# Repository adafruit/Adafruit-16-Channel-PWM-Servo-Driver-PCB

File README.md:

## Adafruit 16-Channel PWM Servo Driver PCB Eagle Files

<a href="http://www.adafruit.com/products/815"><br/>
Click here to purchase one from the Adafruit shop</a>

This is the PCB for the Adafruit 16-channel PWM/Servo breakout board. Format is EagleCAD schematic and board layout
For more details, check out the product page at
* http://www.adafruit.com/products/815

### Description

You want to make a cool robot, maybe a hexapod walker, or maybe just a piece of art with a lot of moving parts. Or maybe you want to drive a lot of LEDs with precise PWM output. Then you realize that your microcontroller has a limited number of PWM outputs! What now? You could give up OR you could just get this handy PWM and Servo driver breakout.

When we saw this chip, we quickly realized what an excellent add-on this would be. Using only two pins, control 16 free-running PWM outputs! You can even chain up 62 breakouts to control up to 992 PWM outputs (which we would really like to see since it would be glorious)

* It's an i2c-controlled PWM driver with a built in clock. That means that, unlike the TLC5940 family, you do not need to continuously send it signal tying up your microcontroller, its completely free running!
* It is 5V compliant, which means you can control it from a 3.3V microcontroller and still safely drive up to 6V outputs (this is good for when you want to control white or blue LEDs with 3.4+ forward voltages)
* 6 address select pins so you can wire up to 62 of these on a single i2c bus, a total of 992 outputs - that's a lot of servos or LEDs
Adjustable frequency PWM up to about 1.6 KHz
* 12-bit resolution for each output - for servos, that means about 4us resolution at 60Hz update rate
* Configurable push-pull or open-drain output
* Output enable pin to quickly disable all the outputs

We wrapped up this lovely chip into a breakout board with a couple nice extras

* Terminal block for power input (or you can use the 0.1" breakouts on the side)
* Reverse polarity protection on the terminal block input. The terminal block included with your product may be blue or black.
* Green power-good LED
* 3 pin connectors in groups of 4 so you can plug in 16 servos at once (Servo plugs are slightly wider than 0.1" so you can only stack 4 next to each other on 0.1" header
* "Chain-able" design
* A spot to place a big capacitor on the V+ line (in case you need it)
* 220 ohm series resistors on all the output lines to protect them, and to make driving LEDs trivial
* Solder jumpers for the 6 address select pins

This product comes with a fully tested and assembled breakout as well as 4 pieces of 3x4 male straight header (for servo/LED plugs), a 2-pin terminal block (for power) and a piece of 6-pin 0.1" header (to plug into a breadboard). A little light soldering will be required to assemble and customize the board by attaching the desired headers but it is a 15 minute task that even a beginner can do.

### License

Adafruit invests time and resources providing this open source design, please support Adafruit and open-source hardware by purchasing products from [Adafruit](https://www.adafruit.com)!

Designed by Limor Fried/Ladyada for Adafruit Industries.

Creative Commons Attribution/Share-Alike, all text above must be included in any redistribution. See license.txt for additional details.

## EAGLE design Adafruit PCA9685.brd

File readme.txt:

This is the PCB for the Adafruit 16-channel PWM/Servo breakout board
Format is EagleCAD schematic and board layout

For more details, check out the product page at

-----> http://www.adafruit.com/products/815

Adafruit invests time and resources providing this open source design, 
please support Adafruit and open-source hardware by purchasing 
products from Adafruit!

Designed by Adafruit Industries.  
Creative Commons Attribution, Share-Alike license, check license.txt for more information
All text above must be included in any redistribution

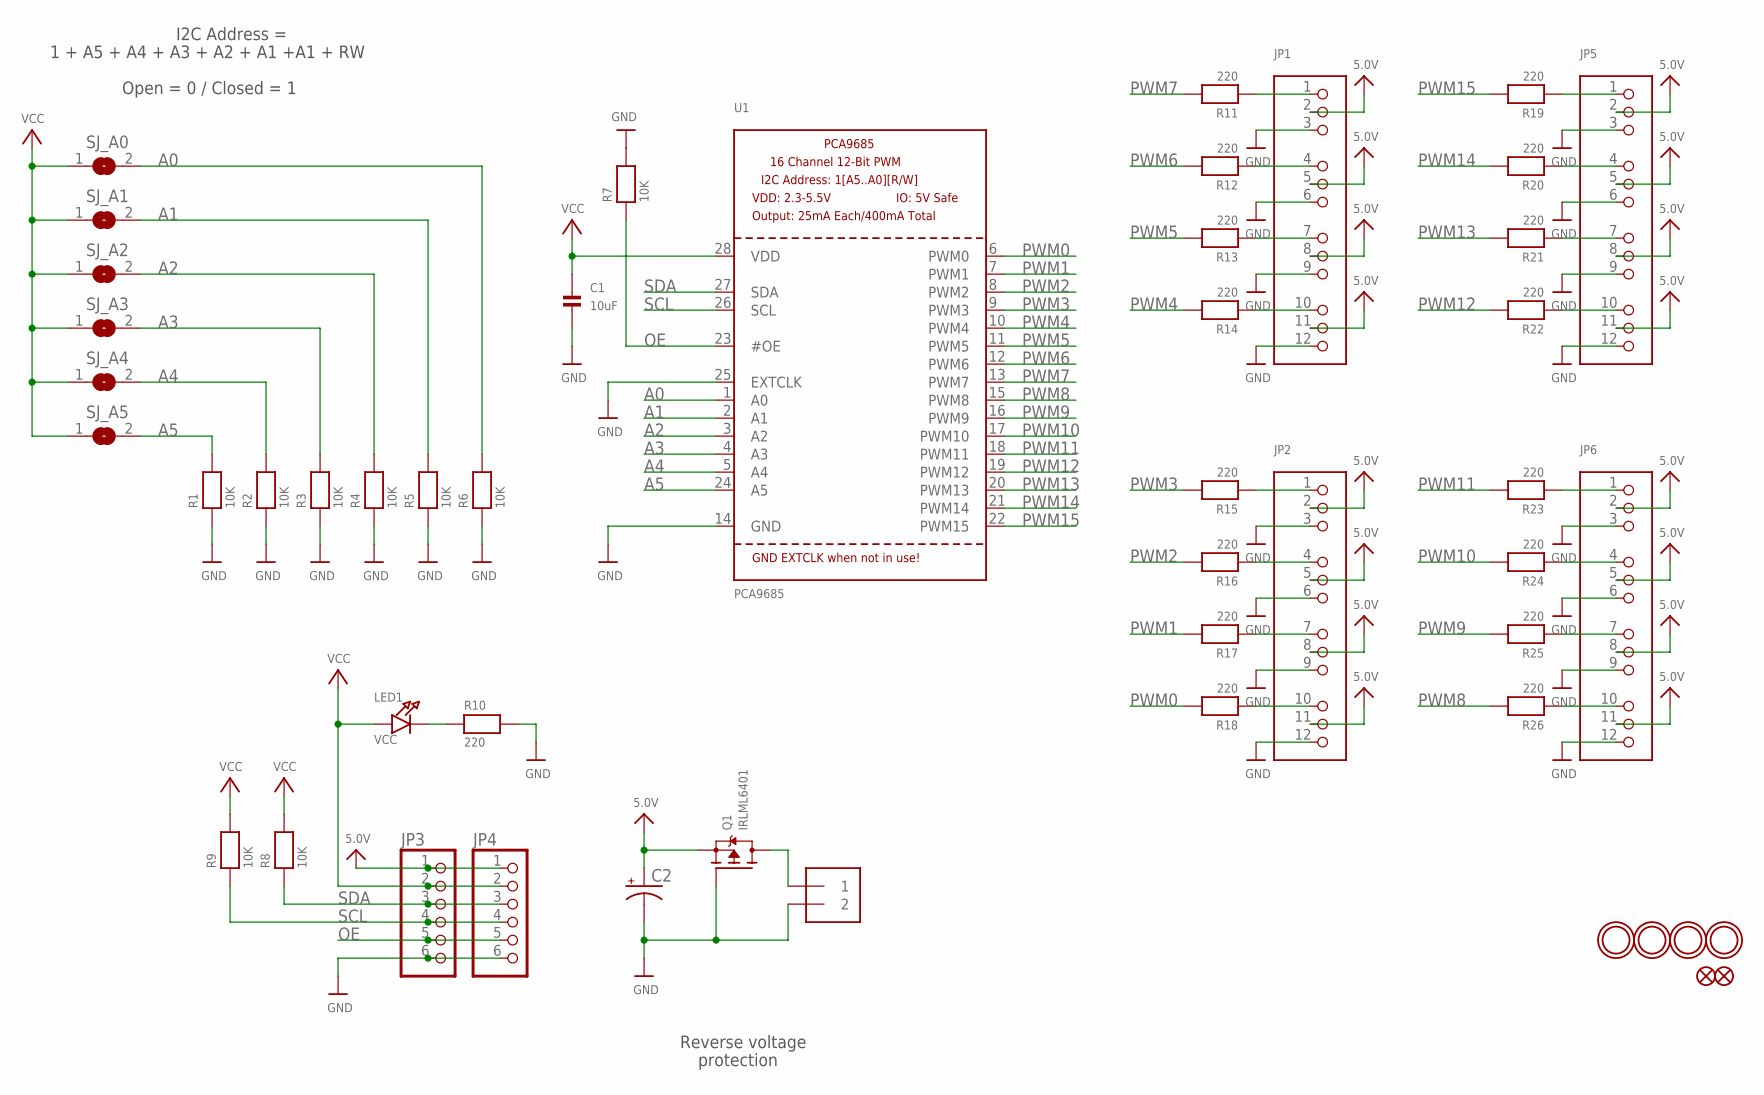
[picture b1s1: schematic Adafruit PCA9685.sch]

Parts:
C1: 10uF; 0805
C2: CPOL-USE3.5-8; E3,5-8
FID1, FID2: FIDUCIAL""; FIDUCIAL_1MM
J1: TERMBLOCK_1X2-3.5MM; 1X2-3.5MM
JP1, JP2, JP5, JP6: HEADER-3X04; 3X04
JP3, JP4: PINHD-1X6CB; 1X06-CLEANBIG
LED1: VCC; CHIPLED_0805
Q1: IRLML6401; SOT23-WIDE
R1, R2, R3, R4, R5, R6, R7, R8, R9: 10K; 0805
R10, R11, R12, R13, R14, R15, R16, R17, R18, R19, R20, R21, R22, R23, R24, R25, R26: 220; 0805
SJ_A0, SJ_A1, SJ_A2, SJ_A3, SJ_A4, SJ_A5: SOLDERJUMPERREFLOW_NOPASTE; SOLDERJUMPER_REFLOW_NOPASTE
U1: PCA9685; TSSOP28
U$47, U$48, U$49, U$50: MOUNTINGHOLE2.5; MOUNTINGHOLE_2.5_PLATED

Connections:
5.0V: C2.+, JP1.2, JP1.5, JP1.8, JP1.11, JP2.2, JP2.5, JP2.8, JP2.11, JP3.1, JP4.1, JP5.2, JP5.5, JP5.8, JP5.11, JP6.2, JP6.5, JP6.8, JP6.11, Q1.2 (S)
A0: R6.2, SJ_A0.2, U1.1 (A0)
A1: R5.2, SJ_A1.2, U1.2 (A1)
A2: R4.2, SJ_A2.2, U1.3 (A2)
A3: R3.2, SJ_A3.2, U1.4 (A3)
A4: R2.2, SJ_A4.2, U1.5 (A4)
A5: R1.2, SJ_A5.2, U1.24 (A5)
GND: C1.2, C2.-, J1.2, JP1.3, JP1.6, JP1.9, JP1.12, JP2.3, JP2.6, JP2.9, JP2.12, JP3.6, JP4.6, JP5.3, JP5.6, JP5.9, JP5.12, JP6.3, JP6.6, JP6.9, JP6.12, Q1.1 (G), R1.1, R2.1, R3.1, R4.1, R5.1, R6.1, R7.2, R10.2, U1.14 (GND), U1.25 (EXTCLK)
unnamed: LED1.C, R10.1
unnamed: JP1.4, R12.1
unnamed: JP1.1, R11.1
unnamed: JP1.7, R13.1
unnamed: JP1.10, R14.1
unnamed: JP2.1, R15.1
unnamed: JP2.4, R16.1
unnamed: JP2.7, R17.1
unnamed: JP2.10, R18.1
unnamed: JP6.10, R26.1
unnamed: JP6.7, R25.1
unnamed: JP6.4, R24.1
unnamed: JP6.1, R23.1
unnamed: JP5.10, R22.1
unnamed: JP5.7, R21.1
unnamed: JP5.4, R20.1
unnamed: JP5.1, R19.1
OE: JP3.5, JP4.5, R7.1, U1.23 (#OE)
PWM0: R18.2, U1.6 (PWM0)
PWM1: R17.2, U1.7 (PWM1)
PWM2: R16.2, U1.8 (PWM2)
PWM3: R15.2, U1.9 (PWM3)
PWM4: R14.2, U1.10 (PWM4)
PWM5: R13.2, U1.11 (PWM5)
PWM6: R12.2, U1.12 (PWM6)
PWM7: R11.2, U1.13 (PWM7)
PWM8: R26.2, U1.15 (PWM8)
PWM9: R25.2, U1.16 (PWM9)
PWM10: R24.2, U1.17 (PWM10)
PWM11: R23.2, U1.18 (PWM11)
PWM12: R22.2, U1.19 (PWM12)
PWM13: R21.2, U1.20 (PWM13)
PWM14: R20.2, U1.21 (PWM14)
PWM15: R19.2, U1.22 (PWM15)
PWRIN: J1.1, Q1.3 (D)
SCL: JP3.4, JP4.4, R9.1, U1.26 (SCL)
SDA: JP3.3, JP4.3, R8.1, U1.27 (SDA)
VCC: C1.1, JP3.2, JP4.2, LED1.A, R8.2, R9.2, SJ_A0.1, SJ_A1.1, SJ_A2.1, SJ_A3.1, SJ_A4.1, SJ_A5.1, U1.28 (VDD)

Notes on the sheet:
Reverse voltage
protection
1 + A5 + A4 + A3 + A2 + A1 +A1 + RW
I2C Address =
Open = 0 / Closed = 1

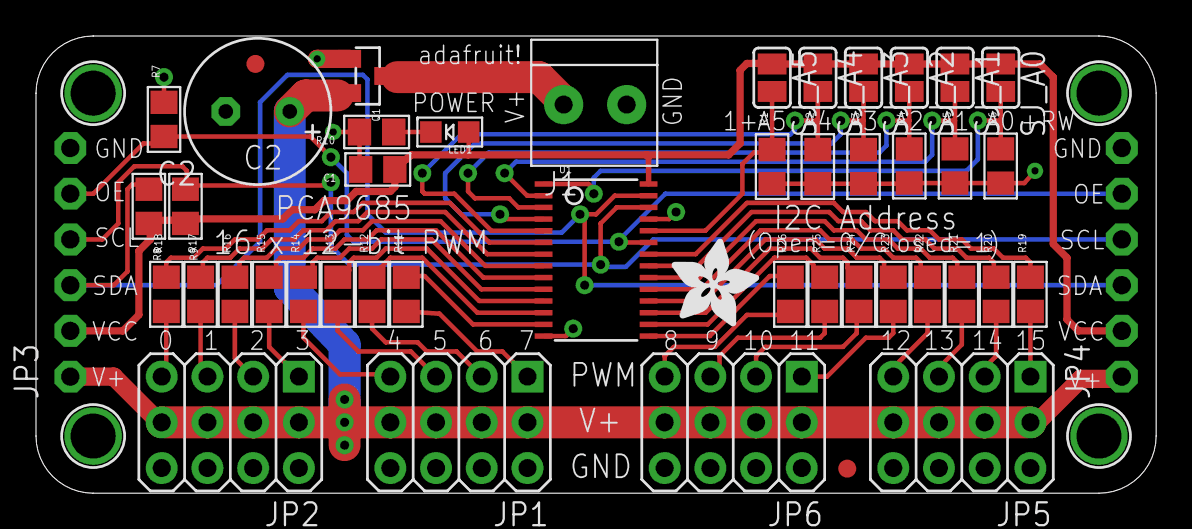
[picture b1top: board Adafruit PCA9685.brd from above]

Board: 2 copper layers, 62.2 x 25.4 mm, 51 parts (0 on the bottom side), 46 nets.

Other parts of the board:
U$51: ADAFRUIT_5MM

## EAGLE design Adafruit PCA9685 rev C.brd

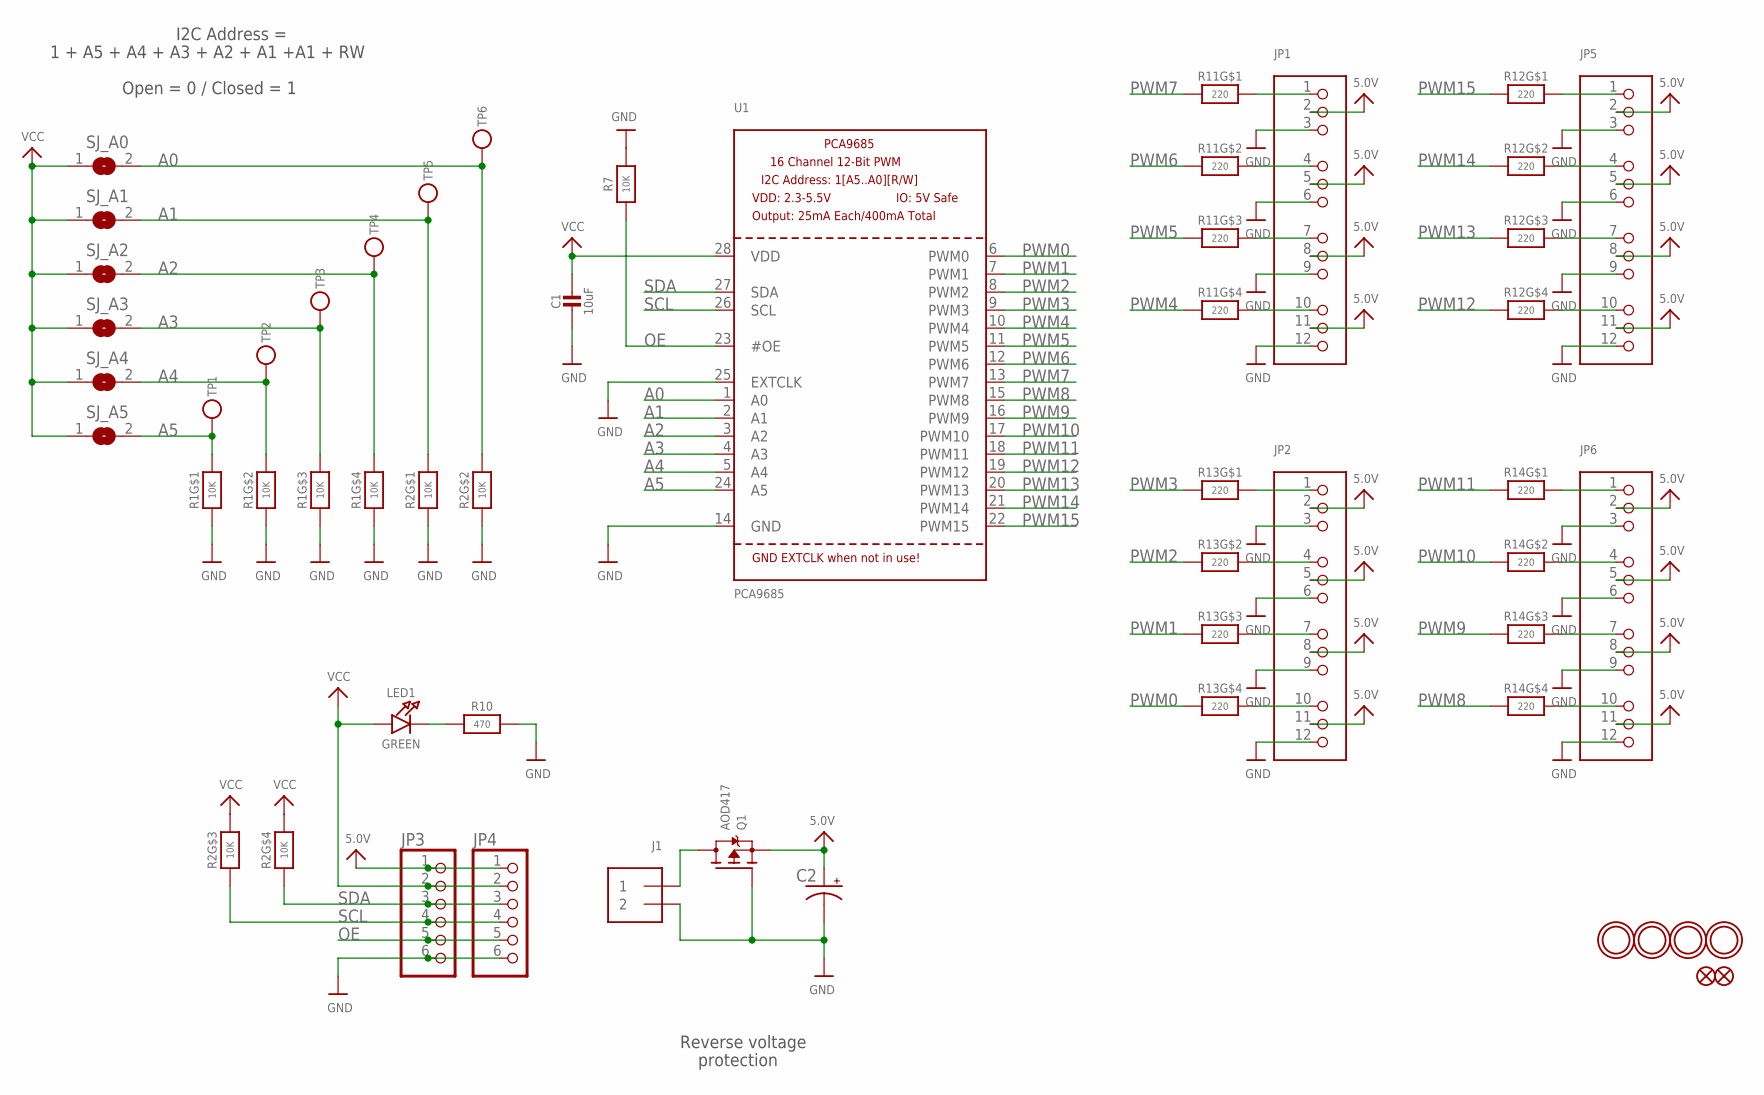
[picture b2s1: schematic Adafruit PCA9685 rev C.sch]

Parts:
C1: 10uF; 0805-NO
C2: CPOL-USE3.5-8; E3,5-8
FID1, FID2: FIDUCIAL""; FIDUCIAL_1MM
J1: TERMBLOCK_1X2; TERMBLOCK_1X2-3.5MM
JP1, JP2, JP5, JP6: HEADER-3X04; 3X04
JP3, JP4: PINHD-1X6CB; 1X06-CLEANBIG
LED1: GREEN; CHIPLED_0805_NOOUTLINE
Q1: AOD417; TO252
R1, R2: 10K; RESPACK_4X0603
R7: 10K; 0805-NO
R10: 470; _0805MP
R11, R12, R13, R14: 220; RESPACK_4X0603
SJ_A0, SJ_A1, SJ_A2, SJ_A3, SJ_A4, SJ_A5: SOLDERJUMPERREFLOW_NOPASTE; SOLDERJUMPER_REFLOW_NOPASTE
TP1, TP2, TP3, TP4, TP5, TP6: TESTPOINTROUND1MM; TESTPOINT_ROUND_1MM
U1: PCA9685; TSSOP28
U$47, U$48, U$49, U$50: MOUNTINGHOLE2.5; MOUNTINGHOLE_2.5_PLATED

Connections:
5.0V: C2.+, JP1.2, JP1.5, JP1.8, JP1.11, JP2.2, JP2.5, JP2.8, JP2.11, JP3.1, JP4.1, JP5.2, JP5.5, JP5.8, JP5.11, JP6.2, JP6.5, JP6.8, JP6.11, Q1.2 (S)
A0: R2.7 (2), SJ_A0.2, TP6.P$1, U1.1 (A0)
A1: R2.8 (2), SJ_A1.2, TP5.P$1, U1.2 (A1)
A2: R1.5 (2), SJ_A2.2, TP4.P$1, U1.3 (A2)
A3: R1.6 (2), SJ_A3.2, TP3.P$1, U1.4 (A3)
A4: R1.7 (2), SJ_A4.2, TP2.P$1, U1.5 (A4)
A5: R1.8 (2), SJ_A5.2, TP1.P$1, U1.24 (A5)
GND: C1.2, C2.-, J1.2, JP1.3, JP1.6, JP1.9, JP1.12, JP2.3, JP2.6, JP2.9, JP2.12, JP3.6, JP4.6, JP5.3, JP5.6, JP5.9, JP5.12, JP6.3, JP6.6, JP6.9, JP6.12, Q1.1 (G), R1.1, R1.2 (1), R1.3 (1), R1.4 (1), R2.1, R2.2 (1), R7.2, R10.2, U1.14 (GND), U1.25 (EXTCLK)
unnamed: LED1.C, R10.1
unnamed: JP1.4, R11.7 (2)
unnamed: JP1.1, R11.8 (2)
unnamed: JP1.7, R11.6 (2)
unnamed: JP1.10, R11.5 (2)
unnamed: JP2.1, R13.8 (2)
unnamed: JP2.4, R13.7 (2)
unnamed: JP2.7, R13.6 (2)
unnamed: JP2.10, R13.5 (2)
unnamed: JP6.10, R14.5 (2)
unnamed: JP6.7, R14.6 (2)
unnamed: JP6.4, R14.7 (2)
unnamed: JP6.1, R14.8 (2)
unnamed: JP5.10, R12.5 (2)
unnamed: JP5.7, R12.6 (2)
unnamed: JP5.4, R12.7 (2)
unnamed: JP5.1, R12.8 (2)
OE: JP3.5, JP4.5, R7.1, U1.23 (#OE)
PWM0: R13.4 (1), U1.6 (PWM0)
PWM1: R13.3 (1), U1.7 (PWM1)
PWM2: R13.2 (1), U1.8 (PWM2)
PWM3: R13.1, U1.9 (PWM3)
PWM4: R11.4 (1), U1.10 (PWM4)
PWM5: R11.3 (1), U1.11 (PWM5)
PWM6: R11.2 (1), U1.12 (PWM6)
PWM7: R11.1, U1.13 (PWM7)
PWM8: R14.4 (1), U1.15 (PWM8)
PWM9: R14.3 (1), U1.16 (PWM9)
PWM10: R14.2 (1), U1.17 (PWM10)
PWM11: R14.1, U1.18 (PWM11)
PWM12: R12.4 (1), U1.19 (PWM12)
PWM13: R12.3 (1), U1.20 (PWM13)
PWM14: R12.2 (1), U1.21 (PWM14)
PWM15: R12.1, U1.22 (PWM15)
PWRIN: J1.1, Q1.3 (D)
SCL: JP3.4, JP4.4, R2.3 (1), U1.26 (SCL)
SDA: JP3.3, JP4.3, R2.4 (1), U1.27 (SDA)
VCC: C1.1, JP3.2, JP4.2, LED1.A, R2.5 (2), R2.6 (2), SJ_A0.1, SJ_A1.1, SJ_A2.1, SJ_A3.1, SJ_A4.1, SJ_A5.1, U1.28 (VDD)

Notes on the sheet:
Reverse voltage
protection
1 + A5 + A4 + A3 + A2 + A1 +A1 + RW
I2C Address =
Open = 0 / Closed = 1

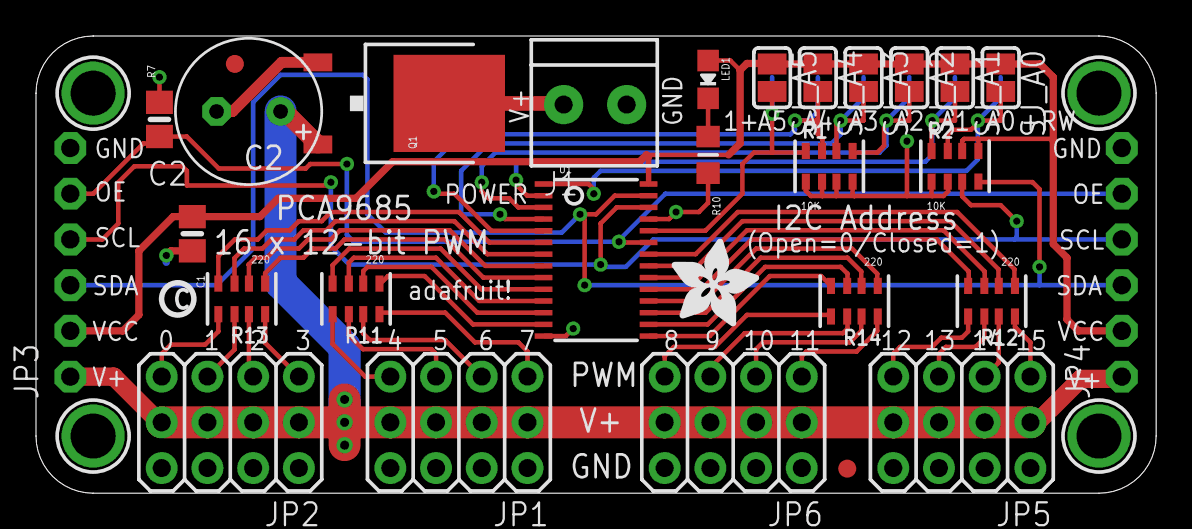
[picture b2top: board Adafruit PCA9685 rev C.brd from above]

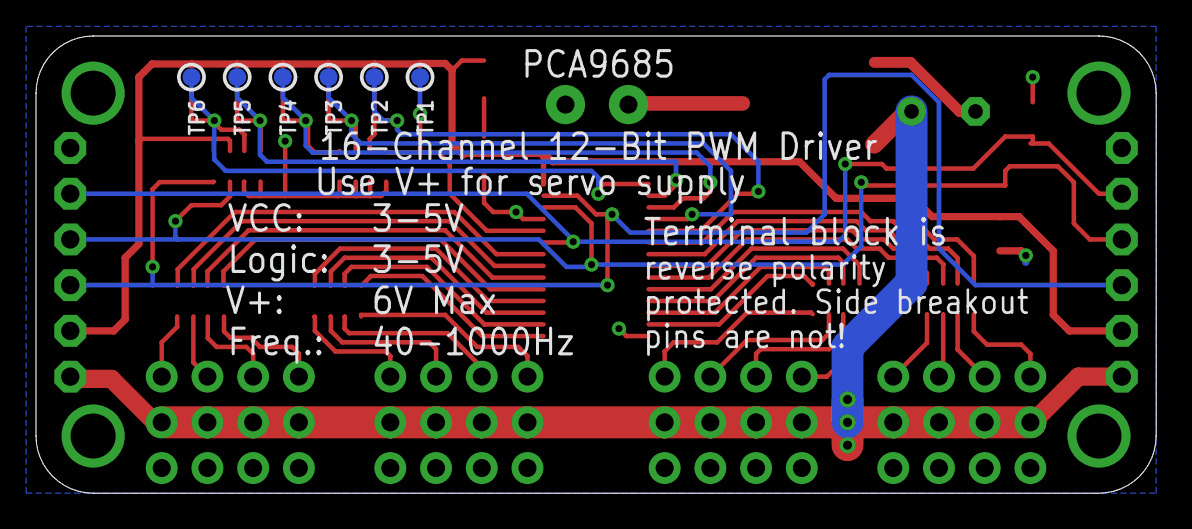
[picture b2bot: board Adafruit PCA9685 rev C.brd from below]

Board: 2 copper layers, 62.2 x 25.4 mm, 40 parts (6 on the bottom side), 46 nets.

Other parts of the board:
U$51: ADAFRUIT_5MM
U$54: PCBFEAT-REV-040

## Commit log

2012-08-27 init
2012-08-27 read!
2013-08-27 Added a .png version of schematic
2018-01-15 updated!
2019-07-03 Rename readme.txt to README.md
2026-06-03 update file format to XML
